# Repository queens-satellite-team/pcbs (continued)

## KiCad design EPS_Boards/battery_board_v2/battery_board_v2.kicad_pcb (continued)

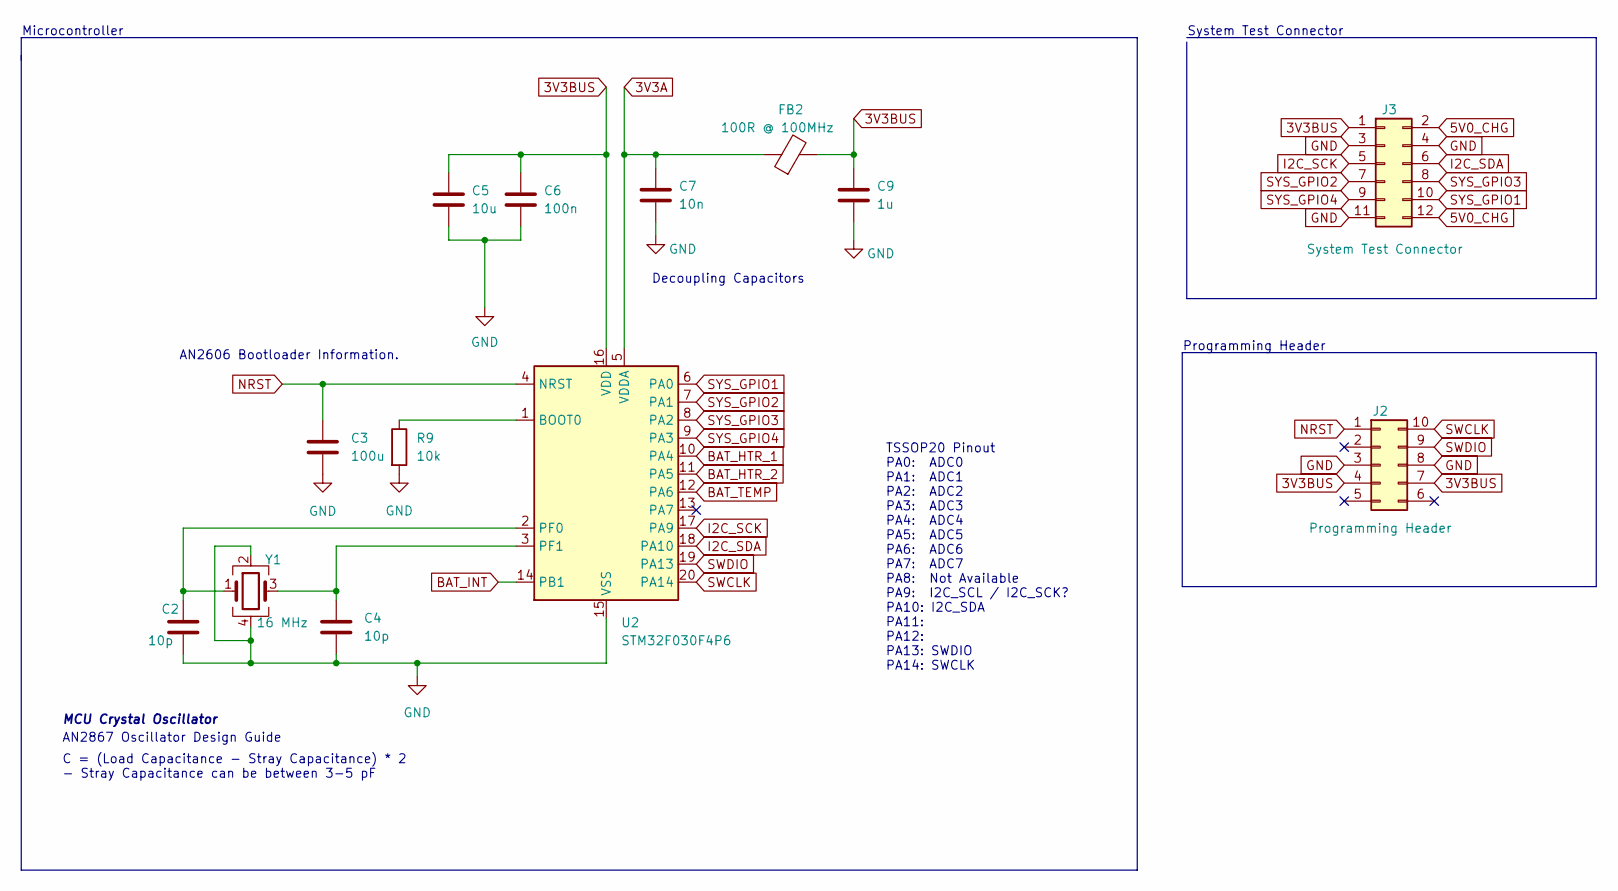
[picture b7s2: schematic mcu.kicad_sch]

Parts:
C2, C4: 10p; C_0402_1005Metric
C3: 100u; C_0402_1005Metric
C5: 10u; C_0402_1005Metric
C6: 100n; C_0402_1005Metric
C7: 10n; C_0402_1005Metric
C9: 1u; C_0402_1005Metric
FB2: 100R @ 100MHz; L_0402_1005Metric
J2: Programming Header; PinSocket_2x05_P2.54mm_Vertical
J3: System Test Connector; PinSocket_2x06_P2.54mm_Vertical
R9: 10k; R_0402_1005Metric
U2: STM32F030F4P6; TSSOP-20_4.4x6.5mm_P0.65mm
Y1: 16 MHz; Crystal_SMD_3225-4Pin_3.2x2.5mm

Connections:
3V3A: C7.1, FB2.1, U2.5 (VDDA)
3V3BUS: C5.1, C6.1, C9.1, FB2.2, J2.4, J2.7, J3.1, U2.16 (VDD); also elsewhere on the board
5V0_CHG: J3.2, J3.12; also elsewhere on the board
BAT_HTR_1: U2.10 (PA4); also elsewhere on the board
BAT_HTR_2: U2.11 (PA5); also elsewhere on the board
BAT_INT: U2.14 (PB1); also elsewhere on the board
BAT_TEMP: U2.12 (PA6); also elsewhere on the board
GND: C2.2, C3.2, C4.2, C5.2, C6.2, C7.2, C9.2, J2.3, J2.8, J3.3, J3.4, J3.11, R9.2, U2.15 (VSS), Y1.2, Y1.4; also elsewhere on the board
I2C_SCK: J3.5, U2.17 (PA9); also elsewhere on the board
I2C_SDA: J3.6, U2.18 (PA10); also elsewhere on the board
NRST: C3.1, J2.1, U2.4 (NRST)
unnamed: C2.1, U2.2 (PF0), Y1.1
unnamed: C4.1, U2.3 (PF1), Y1.3
unnamed: R9.1, U2.1 (BOOT0)
SWCLK: J2.10, U2.20 (PA14)
SWDIO: J2.9, U2.19 (PA13)
SYS_GPIO1: J3.10, U2.6 (PA0)
SYS_GPIO2: J3.7, U2.7 (PA1)
SYS_GPIO3: J3.8, U2.8 (PA2)
SYS_GPIO4: J3.9, U2.9 (PA3)

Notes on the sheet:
System Test Connector
AN2867 Oscillator Design Guide
C = (Load Capacitance - Stray Capacitance) * 2 - Stray Capacitance can be between 3-5 pF
Programming Header
Decoupling Capacitors
TSSOP20 Pinout PA0: ADC0 PA1: ADC1 PA2: ADC2 PA3: ADC3 PA4: ADC4 PA5: ADC5 PA6: ADC6 PA7: ADC7 PA8: Not Available PA9: I2C_SCL / I2C_SCK? PA10: I2C_SDA PA11: PA12: PA13: SWDIO PA14: SWCLK
MCU Crystal Oscillator
Microcontroller
AN2606 Bootloader Information.

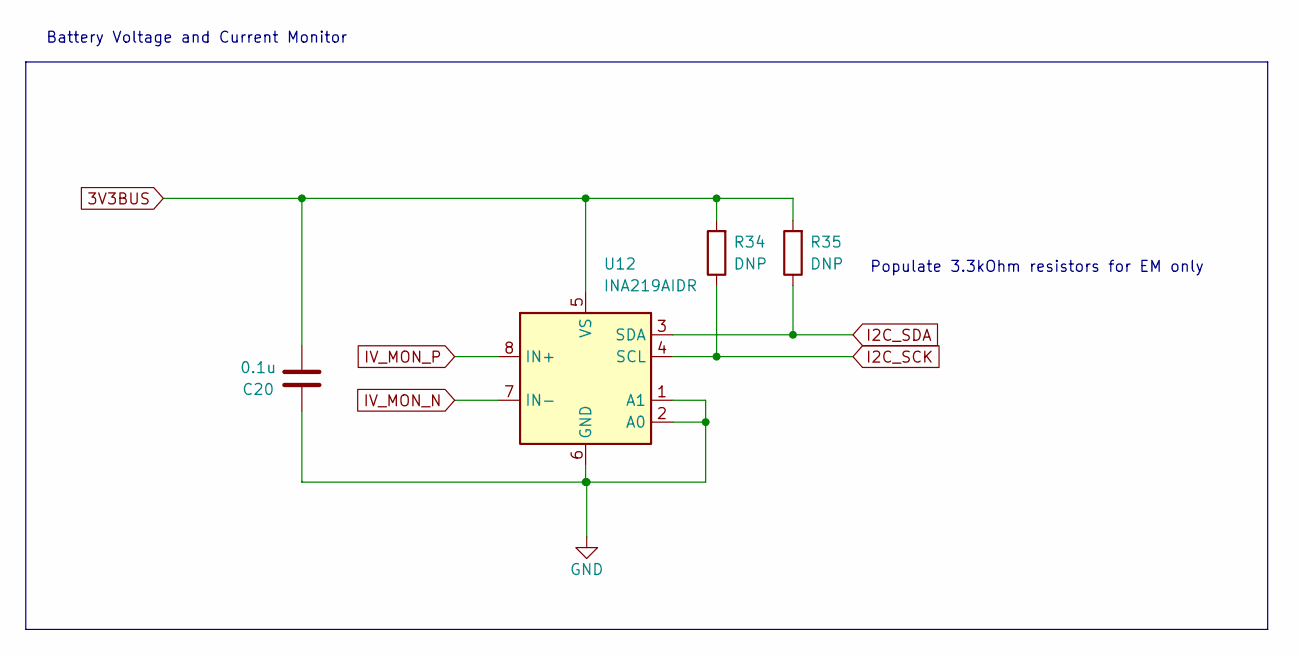
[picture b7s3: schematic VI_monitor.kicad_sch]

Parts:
C20: 0.1u; C_0402_1005Metric
R34, R35: DNP; R_0402_1005Metric
U12: INA219AIDR; SOIC-8_3.9x4.9mm_P1.27mm

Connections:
3V3BUS: C20.2, R34.2, R35.2, U12.5 (VS); also elsewhere on the board
BCR_OUT: U12.8 (IN+); also elsewhere on the board
GND: C20.1, U12.1 (A1), U12.2 (A0), U12.6 (GND); also elsewhere on the board
I2C_SCK: R34.1, U12.4 (SCL); also elsewhere on the board
I2C_SDA: R35.1, U12.3 (SDA); also elsewhere on the board
IV_MON_N: U12.7 (IN-); also elsewhere on the board

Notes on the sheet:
Battery Voltage and Current Monitor
Populate 3.3kOhm resistors for EM only

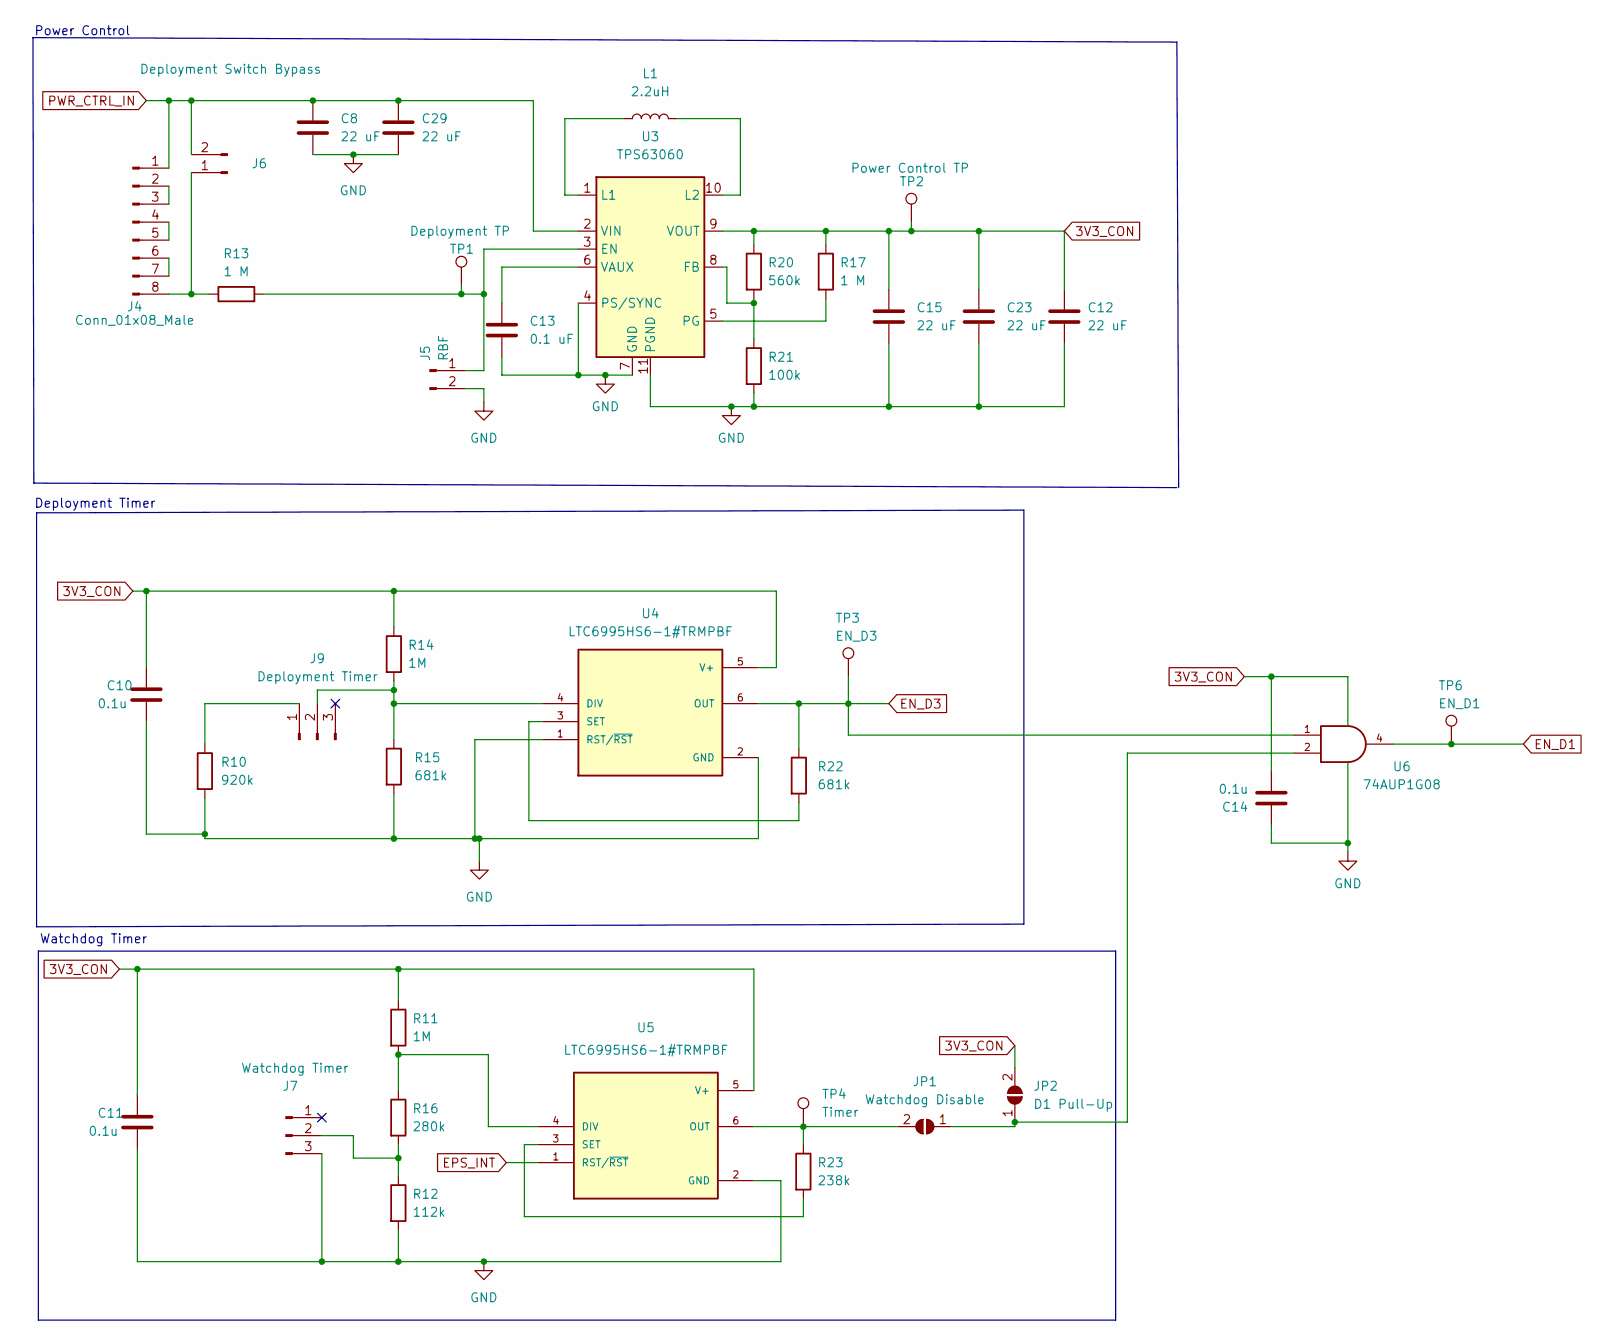
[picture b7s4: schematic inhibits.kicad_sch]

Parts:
C8, C12, C15, C23, C29: 22 uF; C_0402_1005Metric
C10, C11: 0.1u; C_0402_1005Metric
C13: 0.1 uF; C_0402_1005Metric
C14: 0.1u; C_0603_1608Metric
J4: Conn_01x08_Male; M80-5300842
J5: RBF; PinHeader_1x02_P2.00mm_Horizontal
J6: Deployment Switch Bypass; PinHeader_1x02_P2.00mm_Horizontal
J7: Watchdog Timer; PinHeader_1x03_P2.00mm_Horizontal
J9: Deployment Timer; PinHeader_1x03_P2.00mm_Horizontal
JP1: Watchdog Disable; SolderJumper-2_P1.3mm_Open_Pad1.0x1.5mm
JP2: D1 Pull-Up; SolderJumper-2_P1.3mm_Open_Pad1.0x1.5mm
L1: 2.2uH; L_0805_2012Metric_Pad1.15x1.40mm_HandSolder
R10: 920k; R_0402_1005Metric
R11, R14: 1M; R_0402_1005Metric
R12: 112k; R_0402_1005Metric
R13: 1 M; R_0603_1608Metric
R15, R22: 681k; R_0402_1005Metric
R16: 280k; R_0402_1005Metric
R17: 1 M; R_0402_1005Metric
R20: 560k; R_0402_1005Metric
R21: 100k; R_0402_1005Metric
R23: 238k; R_0402_1005Metric
TP1: Deployment TP; TestPoint_THTPad_D2.0mm_Drill1.0mm
TP2: Power Control TP; TestPoint_THTPad_D2.0mm_Drill1.0mm
TP3: EN_D3; TestPoint_THTPad_D2.0mm_Drill1.0mm
TP4: Timer; TestPoint_THTPad_D2.0mm_Drill1.0mm
TP6: EN_D1; TestPoint_THTPad_D2.0mm_Drill1.0mm
U3: TPS63060; Texas_S-PWSON-N10_ThermalVias
U4, U5: LTC6995HS6-1#TRMPBF; DFN-6_DCB_LIT; PARTREV Rev. B
U6: 74AUP1G08; SOT-353_SC-70-5_Handsoldering

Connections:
3V3_CON: C10.1, C11.1, C12.1, C14.2, C15.1, C23.1, JP2.2 (B), R11.1, R14.1, R17.1, R20.1, TP2.1, U3.9 (VOUT), U4.5 (V+), U5.5 (V+), U6.5 (VCC)
BCR_OUT: C8.1, C29.1, J4.1, J6.2, U3.2 (VIN); also elsewhere on the board
EN_D1: TP6.1, U6.4; also elsewhere on the board
EN_D3: R22.1, TP3.1, U4.6 (OUT), U6.1; also elsewhere on the board
EPS_INT: U5.1 (RST/~RST); also elsewhere on the board
GND: C8.2, C10.2, C11.2, C12.2, C13.2, C14.1, C15.2, C23.2, C29.2, J5.2, J7.3, R10.2, R12.2, R15.2, R21.2, U3.4 (PS/SYNC), U3.7 (GND), U3.11 (PGND), U4.1 (RST/~RST), U4.2 (GND), U5.2 (GND), U6.3 (GND); also elsewhere on the board
unnamed: C13.1, U3.6 (VAUX)
unnamed: J4.2, J4.3
unnamed: J4.4, J4.5
unnamed: J4.6, J4.7
unnamed: J4.8, J6.1, R13.1
unnamed: J5.1, R13.2, TP1.1, U3.3 (EN)
unnamed: J7.2, R12.1, R16.2
unnamed: J9.1, R10.1
unnamed: J9.2, R14.2, R15.1, U4.4 (DIV)
unnamed: JP1.1 (A), JP2.1 (A), U6.2
unnamed: JP1.2 (B), R23.1, TP4.1, U5.6 (OUT)
unnamed: L1.1, U3.1 (L1)
unnamed: L1.2, U3.10 (L2)
unnamed: R11.2, R16.1, U5.4 (DIV)
unnamed: R17.2, U3.5 (PG)
unnamed: R20.2, R21.1, U3.8 (FB)
unnamed: R22.2, U4.3 (SET)
unnamed: R23.2, U5.3 (SET)

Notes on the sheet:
Deployment Timer
Watchdog Timer
Power Control

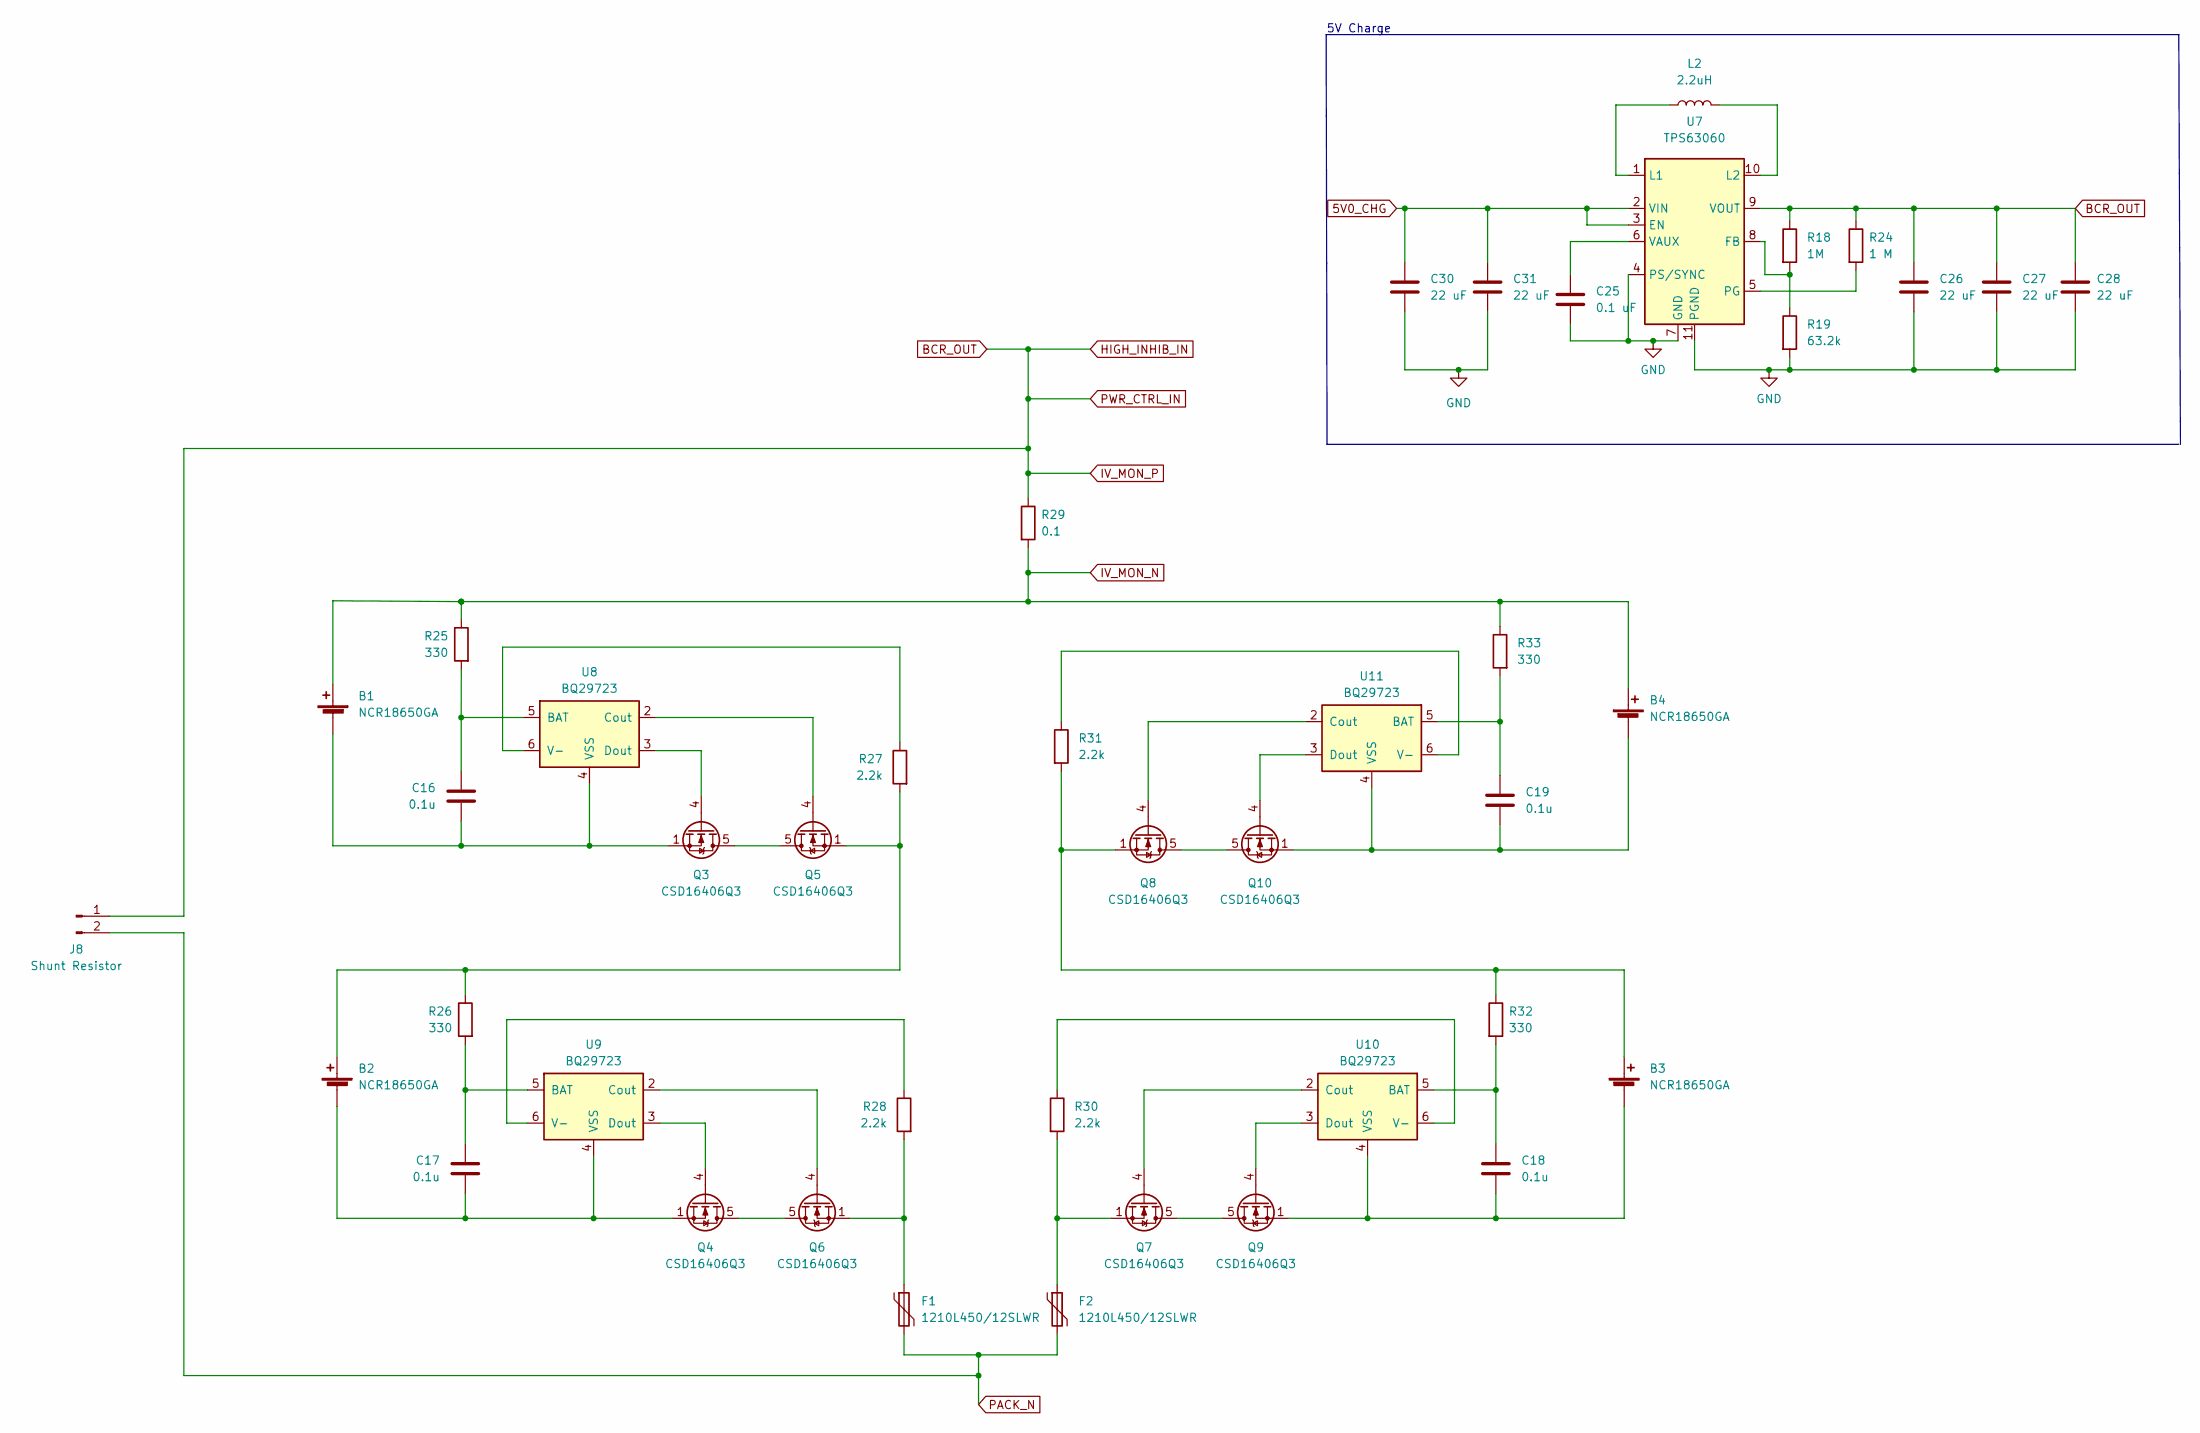
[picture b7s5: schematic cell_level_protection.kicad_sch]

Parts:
B1, B2, B3, B4: NCR18650GA; Keystone_54_18650
C16, C17, C18, C19: 0.1u; C_0402_1005Metric
C25: 0.1 uF; C_01005_0402Metric
C26, C27, C28, C30, C31: 22 uF; C_01005_0402Metric
F1, F2: 1210L450/12SLWR; 1210L450-polyfuse
J8: Shunt Resistor; PinHeader_1x02_P2.00mm_Vertical
L2: 2.2uH; L_0805_2012Metric_Pad1.15x1.40mm_HandSolder
Q3, Q4, Q5, Q6, Q7, Q8, Q9, Q10: CSD16406Q3; TDSON-8-1
R18: 1M; R_0402_1005Metric
R19: 63.2k; R_0402_1005Metric
R24: 1 M; R_0402_1005Metric
R25, R26, R32, R33: 330; R_0402_1005Metric
R27, R28, R30, R31: 2.2k; R_0402_1005Metric
R29: 0.1; R_0402_1005Metric
U7: TPS63060; Texas_S-PWSON-N10_ThermalVias
U8, U9, U10, U11: BQ29723; WSON-6_1.5x1.5mm_P0.5mm

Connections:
5V0_CHG: C30.1, C31.1, U7.2 (VIN), U7.3 (EN); also elsewhere on the board
BCR_OUT: C26.1, C27.1, C28.1, J8.1, R18.1, R24.1, R29.1, U7.9 (VOUT); also elsewhere on the board
GND: C25.2, C26.2, C27.2, C28.2, C30.2, C31.2, R19.2, U7.4 (PS/SYNC), U7.7 (GND), U7.11 (PGND); also elsewhere on the board
IV_MON_N: B1.1 (+), B4.1 (+), R25.1, R29.2, R33.1; also elsewhere on the board
unnamed: B1.2 (-), C16.1, Q3.1 (S), Q3.2 (S), Q3.3 (S), U8.4 (VSS)
unnamed: B2.1 (+), Q5.1 (S), Q5.2 (S), Q5.3 (S), R26.1, R27.2
unnamed: B2.2 (-), C17.1, Q4.1 (S), Q4.2 (S), Q4.3 (S), U9.4 (VSS)
unnamed: B3.1 (+), Q8.1 (S), Q8.2 (S), Q8.3 (S), R31.2, R32.1
unnamed: B3.2 (-), C18.1, Q9.1 (S), Q9.2 (S), Q9.3 (S), U10.4 (VSS)
unnamed: B4.2 (-), C19.1, Q10.1 (S), Q10.2 (S), Q10.3 (S), U11.4 (VSS)
unnamed: C16.2, R25.2, U8.5 (BAT)
unnamed: C17.2, R26.2, U9.5 (BAT)
unnamed: C18.2, R32.2, U10.5 (BAT)
unnamed: C19.2, R33.2, U11.5 (BAT)
unnamed: C25.1, U7.6 (VAUX)
unnamed: F1.1, Q6.1 (S), Q6.2 (S), Q6.3 (S), R28.2
unnamed: F2.1, Q7.1 (S), Q7.2 (S), Q7.3 (S), R30.2
unnamed: L2.1, U7.1 (L1)
unnamed: L2.2, U7.10 (L2)
unnamed: Q3.4 (G), U8.3 (Dout)
unnamed: Q3.5 (D), Q5.5 (D)
unnamed: Q4.4 (G), U9.3 (Dout)
unnamed: Q4.5 (D), Q6.5 (D)
unnamed: Q5.4 (G), U8.2 (Cout)
unnamed: Q6.4 (G), U9.2 (Cout)
unnamed: Q7.4 (G), U10.2 (Cout)
unnamed: Q7.5 (D), Q9.5 (D)
unnamed: Q8.4 (G), U11.2 (Cout)
unnamed: Q9.4 (G), U10.3 (Dout)
unnamed: Q10.4 (G), U11.3 (Dout)
unnamed: Q8.5 (D), Q10.5 (D)
unnamed: R18.2, R19.1, U7.8 (FB)
unnamed: R24.2, U7.5 (PG)
unnamed: R27.1, U8.6 (V-)
unnamed: R28.1, U9.6 (V-)
unnamed: R30.1, U10.6 (V-)
unnamed: R31.1, U11.6 (V-)
PACK_N: F1.2, F2.2, J8.2; also elsewhere on the board

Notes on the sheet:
5V Charge

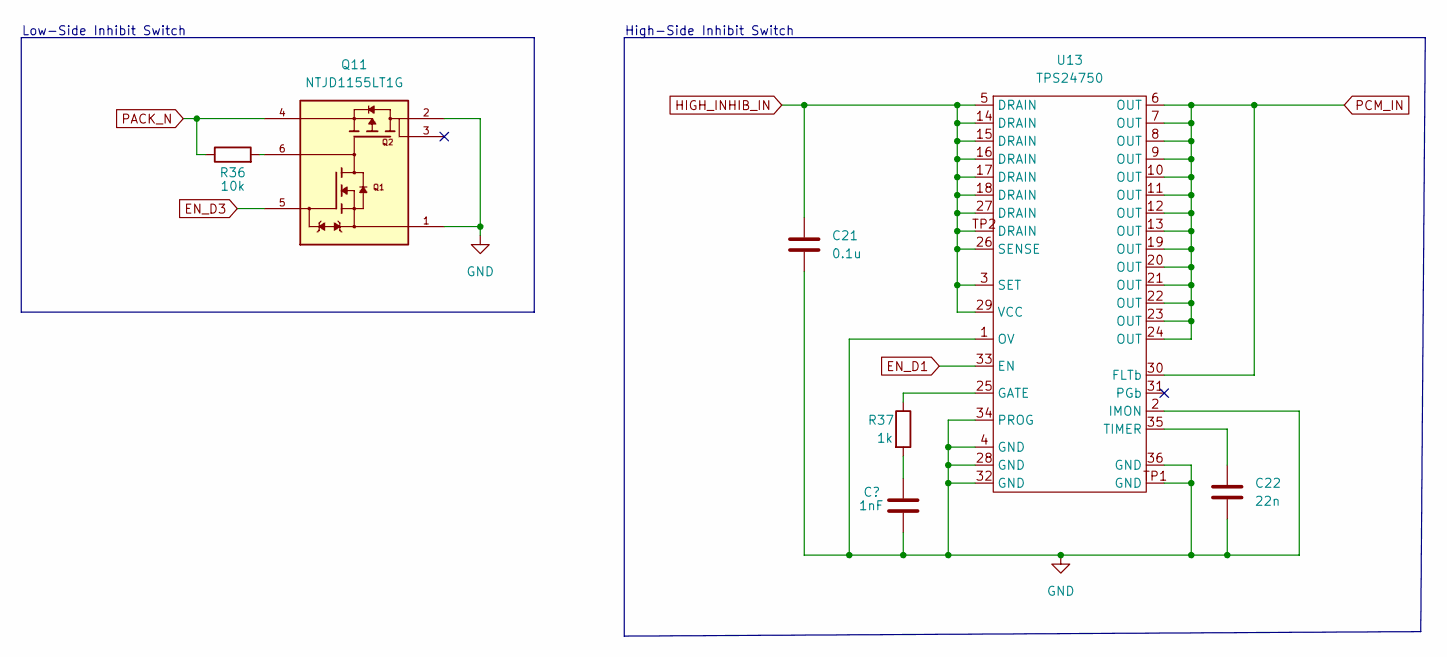
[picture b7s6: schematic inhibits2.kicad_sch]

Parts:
C21: 0.1u; C_01005_0402Metric
C22: 22n; C_01005_0402Metric
Q11: NTJD1155LT1G; TRANS_NTJD1155LT1G; PARTREV Rev. 6
R36: 10k; R_0402_1005Metric
R37: 1k; R_0402_1005Metric
U13: TPS24750

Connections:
BCR_OUT: C21.1, U13.3 (SET), U13.5 (DRAIN), U13.14 (DRAIN), U13.15 (DRAIN), U13.16 (DRAIN), U13.17 (DRAIN), U13.18 (DRAIN), U13.26 (SENSE), U13.27 (DRAIN), U13.29 (VCC), U13.TP2 (DRAIN); also elsewhere on the board
EN_D1: U13.33 (EN); also elsewhere on the board
EN_D3: Q11.5; also elsewhere on the board
GND: C21.2, C22.2, Q11.1, Q11.2, U13.1 (OV), U13.2 (IMON), U13.4 (GND), U13.28 (GND), U13.32 (GND), U13.34 (PROG), U13.36 (GND), U13.TP1 (GND); also elsewhere on the board
unnamed: C22.1, U13.35 (TIMER)
unnamed 33: R37.2; also elsewhere on the board
unnamed: Q11.6, R36.2
unnamed: R37.1, U13.25 (GATE)
PACK_N: Q11.4, R36.1; also elsewhere on the board
PCM_IN: U13.6 (OUT), U13.7 (OUT), U13.8 (OUT), U13.9 (OUT), U13.10 (OUT), U13.11 (OUT), U13.12 (OUT), U13.13 (OUT), U13.19 (OUT), U13.20 (OUT), U13.21 (OUT), U13.22 (OUT), U13.23 (OUT), U13.24 (OUT), U13.30 (FLTb); also elsewhere on the board

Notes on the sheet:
Low-Side Inhibit Switch
High-Side Inhibit Switch

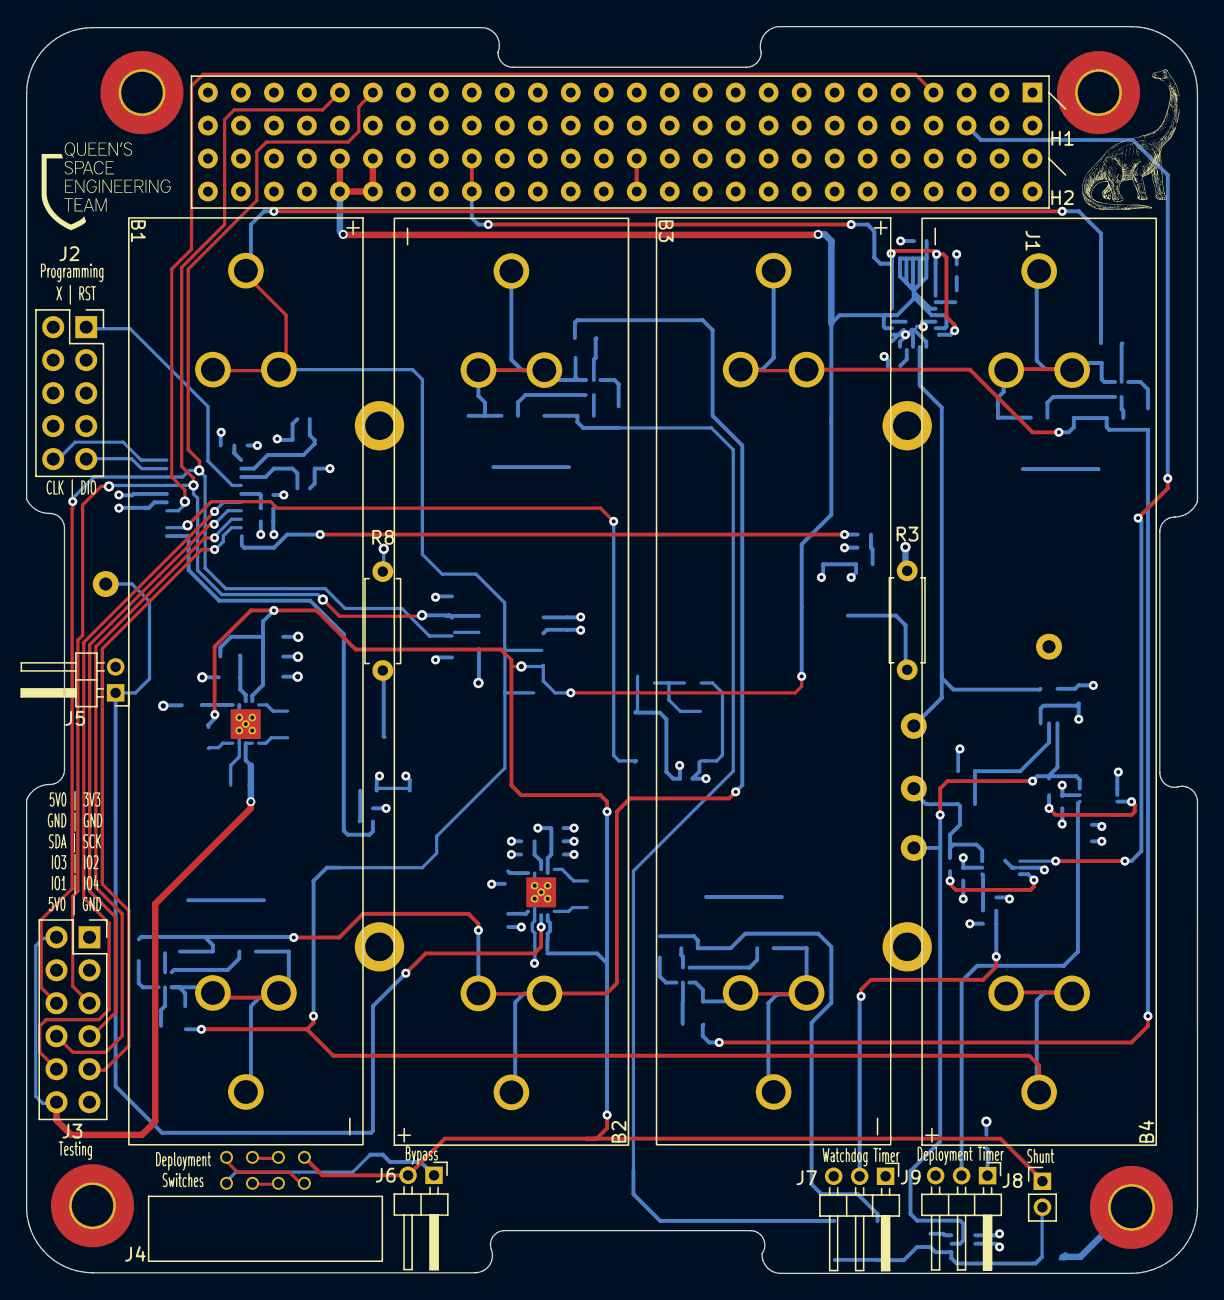
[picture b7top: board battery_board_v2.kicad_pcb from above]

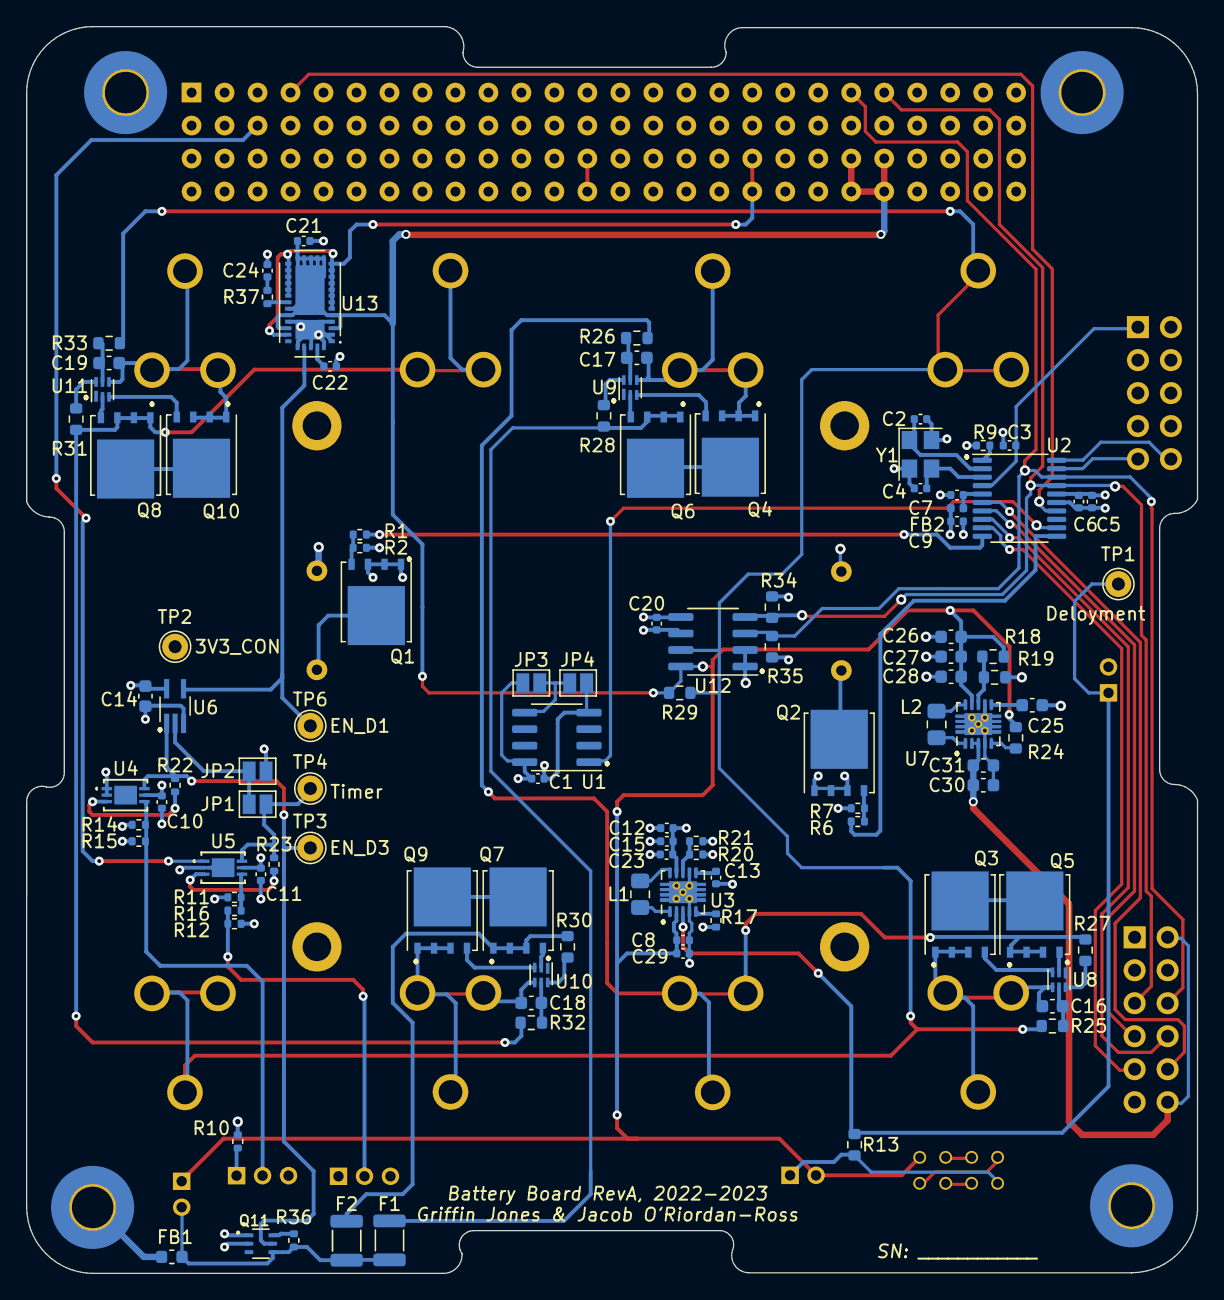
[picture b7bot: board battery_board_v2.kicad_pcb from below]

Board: 4 copper layers, 90.2 x 96.0 mm, 127 parts (104 on the bottom side), 90 nets.

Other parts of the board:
C24: 1nF; C_0402_1005Metric

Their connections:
GND: C24.2; also elsewhere on the board
unnamed 33: C24.1; also elsewhere on the board

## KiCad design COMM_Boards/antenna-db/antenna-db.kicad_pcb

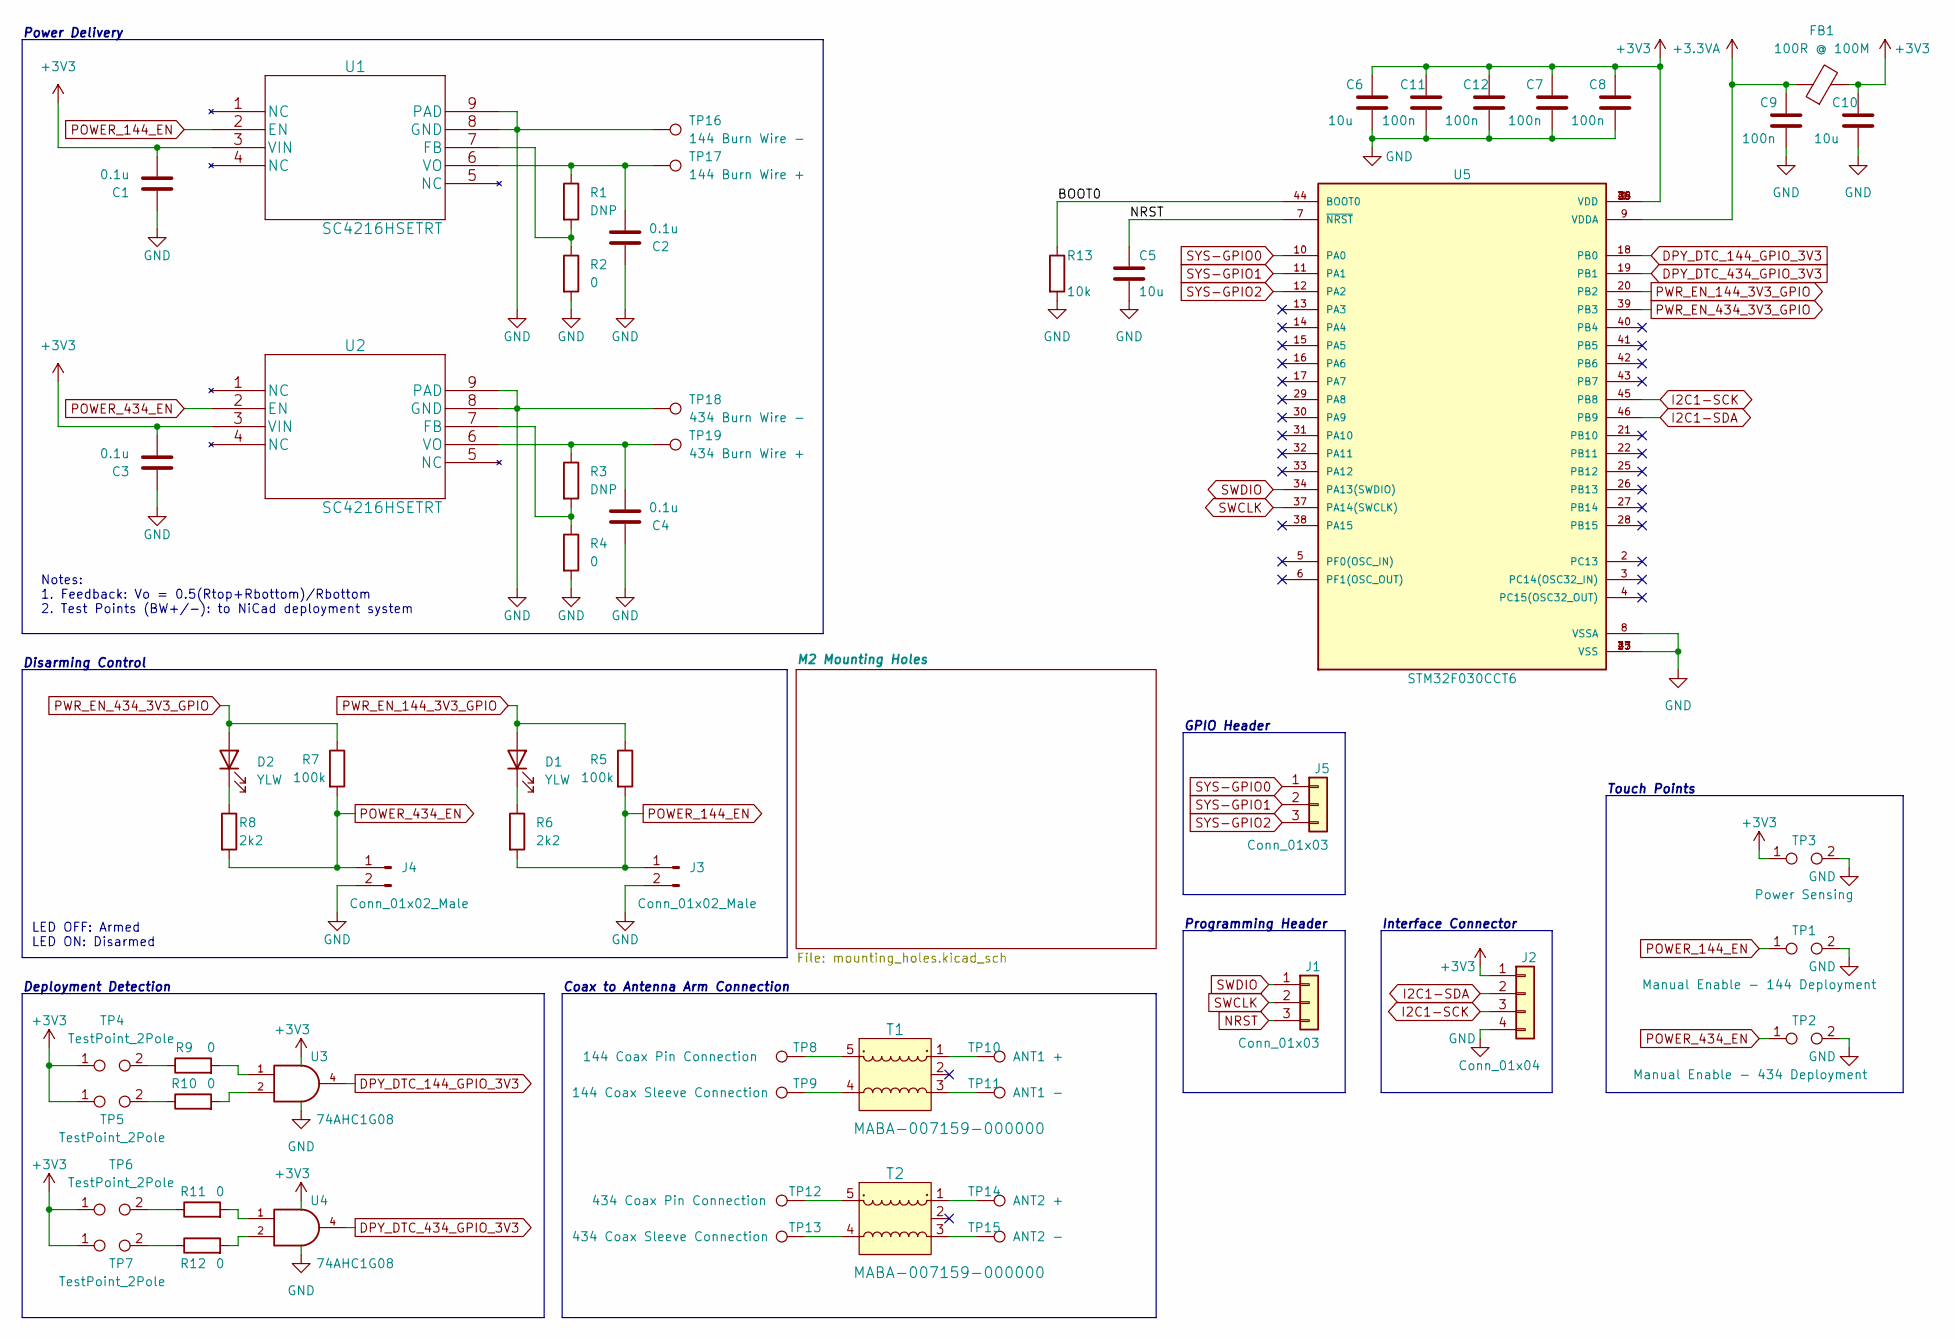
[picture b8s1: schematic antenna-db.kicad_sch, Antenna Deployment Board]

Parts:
C1, C2, C3, C4: 0.1u; C_0603_1608Metric
C5, C6, C10: 10u; C_0603_1608Metric
C7, C8, C9, C11, C12: 100n; C_0603_1608Metric
D1, D2: YLW; LED_0603_1608Metric
FB1: 100R @ 100M; L_0603_1608Metric
J1, J5: Conn_01x03; SAMTEC_TSM-103-01-L-SH
J2: Conn_01x04; SAMTEC_TSM-104-01-L-SH
J3, J4: Conn_01x02_Male; SAMTEC_TSM-102-01-L-SH
R1, R3: DNP; R_0603_1608Metric_Pad0.98x0.95mm_HandSolder
R2, R4: 0; R_0603_1608Metric_Pad0.98x0.95mm_HandSolder
R5, R7: 100k; R_0603_1608Metric
R6, R8: 2k2; R_0603_1608Metric
R9, R10, R11, R12: 0; R_0603_1608Metric
R13: 10k; R_0603_1608Metric
T1, T2: MABA-007159-000000; MPN MABA-007159-000000; Digi-Key_PN 1465-1302-1-ND
TP1: Manual Enable - 144 Deployment; TestPoint_2Pads_Pitch2.54mm_Drill0.8mm
TP2: Manual Enable - 434 Deployment; TestPoint_2Pads_Pitch2.54mm_Drill0.8mm
TP3: Power Sensing; TestPoint_2Pads_Pitch2.54mm_Drill0.8mm
TP4, TP5, TP6, TP7: TestPoint_2Pole; TestPoint_2Pads_Pitch2.54mm_Drill0.8mm
TP8: 144 Coax Pin Connection; TestPoint_THTPad_2.0x2.0mm_Drill1.0mm
TP9: 144 Coax Sleeve Connection; TestPoint_THTPad_2.0x2.0mm_Drill1.0mm
TP10: ANT1 +; TestPoint_THTPad_4.0x4.0mm_Drill2.0mm
TP11: ANT1 -; TestPoint_THTPad_4.0x4.0mm_Drill2.0mm
TP12: 434 Coax Pin Connection; TestPoint_THTPad_2.0x2.0mm_Drill1.0mm
TP13: 434 Coax Sleeve Connection; TestPoint_THTPad_2.0x2.0mm_Drill1.0mm
TP14: ANT2 +; TestPoint_THTPad_4.0x4.0mm_Drill2.0mm
TP15: ANT2 -; TestPoint_THTPad_4.0x4.0mm_Drill2.0mm
TP16: 144 Burn Wire -; TestPoint_THTPad_2.0x2.0mm_Drill1.0mm
TP17: 144 Burn Wire +; TestPoint_THTPad_2.0x2.0mm_Drill1.0mm
TP18: 434 Burn Wire -; TestPoint_THTPad_2.0x2.0mm_Drill1.0mm
TP19: 434 Burn Wire +; TestPoint_THTPad_2.0x2.0mm_Drill1.0mm
U1, U2: SC4216HSETRT; SOIC-8-1EP_3.9x4.9mm_P1.27mm_EP2.29x3mm
U3, U4: 74AHC1G08; SOT-353_SC-70-5
U5: STM32F030CCT6; QFP50P900X900X160-48N

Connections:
+3.3VA: C9.1, FB1.1, U5.9 (VDDA)
+3V3: C1.2, C3.2, C6.1, C7.1, C8.1, C10.1, C11.1, C12.1, FB1.2, J2.1, TP3.1, TP4.1, TP5.1, TP6.1, TP7.1, U1.3 (VIN), U2.3 (VIN), U3.5 (VCC), U4.5 (VCC), U5.1 (VDD), U5.24 (VDD), U5.36 (VDD), U5.48 (VDD)
/BOOT0: R13.1, U5.44 (BOOT0)
DPY_DTC_144_GPIO_3V3: U3.4, U5.18 (PB0)
DPY_DTC_434_GPIO_3V3: U4.4, U5.19 (PB1)
GND: C1.1, C2.1, C3.1, C4.1, C5.2, C6.2, C7.2, C8.2, C9.2, C10.2, C11.2, C12.2, J2.4, J3.2, J4.2, R2.2, R4.2, R13.2, TP1.2, TP2.2, TP3.2, TP16.1, TP18.1, U1.8 (GND), U1.9 (PAD), U2.8 (GND), U2.9 (PAD), U3.3 (GND), U4.3 (GND), U5.8 (VSSA), U5.23 (VSS), U5.35 (VSS), U5.47 (VSS)
I2C1-SCK: J2.3, U5.45 (PB8)
I2C1-SDA: J2.2, U5.46 (PB9)
NRST: C5.1, J1.3, U5.7 (~NRST)
unnamed: C2.2, R1.1, TP17.1, U1.6 (VO)
unnamed: C4.2, R3.1, TP19.1, U2.6 (VO)
unnamed: D1.1 (K), R6.1
unnamed: D2.1 (K), R8.1
unnamed: R1.2, R2.1, U1.7 (FB)
unnamed: R3.2, R4.1, U2.7 (FB)
unnamed: R9.1, TP4.2
unnamed: R10.1, TP5.2
unnamed: R11.1, TP6.2
unnamed: R12.1, TP7.2
unnamed: T1.1, TP10.1
unnamed: T1.3, TP11.1
unnamed: T1.4, TP9.1
unnamed: T1.5, TP8.1
unnamed: T2.1, TP14.1
unnamed: T2.3, TP15.1
unnamed: T2.4, TP13.1
unnamed: T2.5, TP12.1
unnamed: R9.2, U3.1
unnamed: R10.2, U3.2
unnamed: R11.2, U4.1
unnamed: R12.2, U4.2
POWER_144_EN: J3.1, R5.2, R6.2, TP1.1, U1.2 (EN)
POWER_434_EN: J4.1, R7.2, R8.2, TP2.1, U2.2 (EN)
PWR_EN_144_3V3_GPIO: D1.2 (A), R5.1, U5.20 (PB2)
PWR_EN_434_3V3_GPIO: D2.2 (A), R7.1, U5.39 (PB3)
SWCLK: J1.2, U5.37 (PA14(SWCLK))
SWDIO: J1.1, U5.34 (PA13(SWDIO))
SYS-GPIO0: J5.1, U5.10 (PA0)
SYS-GPIO1: J5.2, U5.11 (PA1)
SYS-GPIO2: J5.3, U5.12 (PA2)

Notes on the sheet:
Power Delivery
Deployment Detection
Notes: 1. Feedback: Vo = 0.5(Rtop+Rbottom)/Rbottom 2. Test Points (BW+/-): to NiCad deployment system
LED OFF: Armed LED ON: Disarmed
Touch Points
GPIO Header
Coax to Antenna Arm Connection
Interface Connector
Disarming Control
Programming Header

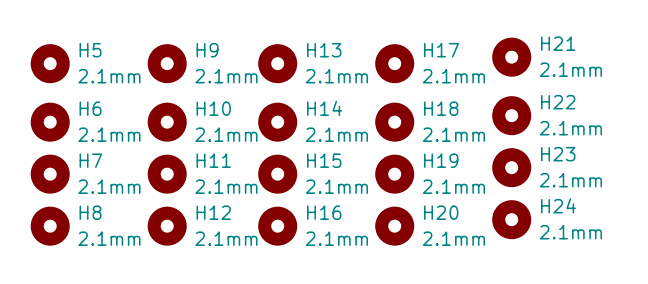
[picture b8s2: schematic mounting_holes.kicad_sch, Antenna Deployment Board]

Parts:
H5, H6, H7, H8, H9, H10, H11, H12, H13, H14, H15, H16, H17, H18, H19, H20, H21, H22, H23, H24: 2.1mm; MountingHole_2.2mm_M2_Pad_TopBottom
